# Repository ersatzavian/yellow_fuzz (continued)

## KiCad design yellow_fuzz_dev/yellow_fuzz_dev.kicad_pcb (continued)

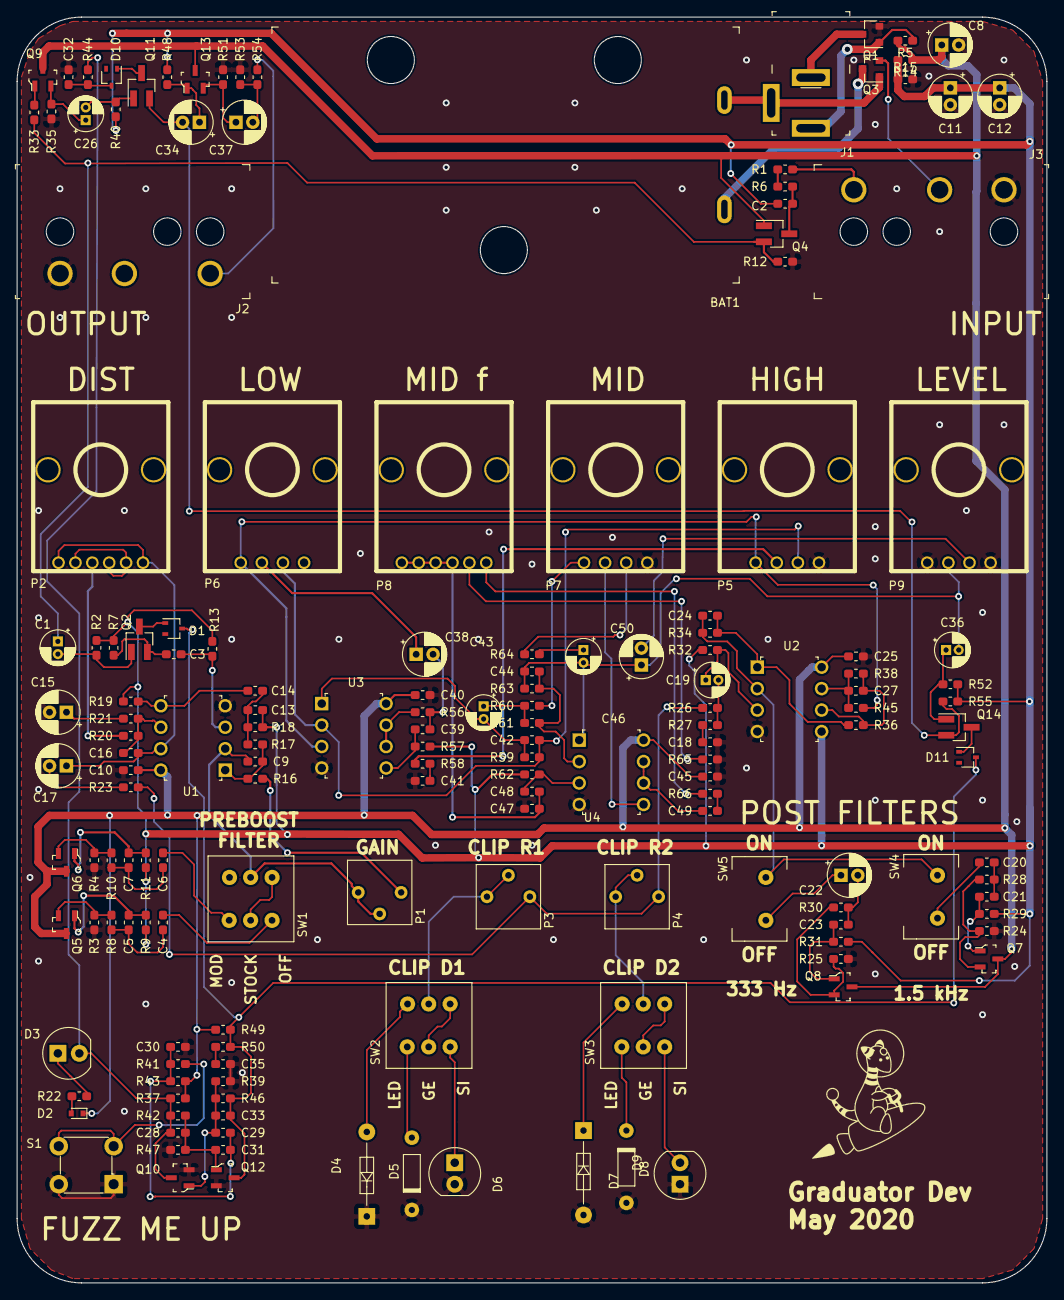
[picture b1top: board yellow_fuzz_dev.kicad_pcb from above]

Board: 2 copper layers, 121.9 x 149.9 mm, 164 parts (0 on the bottom side), 106 nets.

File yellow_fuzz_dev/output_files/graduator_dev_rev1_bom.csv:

"Id";"Designator";"Package";"Quantity";"Designation";"Supplier and ref";
1;"P4,P3";"3362PT";2;"3362P-1-102TLF";;;
2;"C40,C48,C45,C25,C10,C4";"C_0603_1608Metric_Pad1.05x0.95mm_HandSolder";6;"0.1u";;;
3;"G***";"amph_1_5x1_5";1;"LOGO";;;
4;"P9";"Potentiometer_Bourns_PTV111_4420A_Single_Vertical";1;"PTV111-4420A-A503";;;
5;"P8";"Potentiometer_Bourns_PTV112_3417A_Dual_Vertical";1;"PTV112-4420A-A503";;;
6;"P7,P6,P5";"Potentiometer_Bourns_PTV111_4420A_Single_Vertical";3;"PTV111-4420A-A104";;;
7;"P2";"Potentiometer_Bourns_PTV112_3417A_Dual_Vertical";1;"PTV112-4420A-A104";;;
8;"BAT1";"Battery_Holder_9V_BC9VPC-ND";1;"BC9VPC";;;
9;"J2";"Headphone_Jack_6.35mm_SN49B12B";1;"RA49B11";;;
10;"J3";"Headphone_Jack_6.35mm_SN49B12B";1;"SN49B12B";;;
11;"J1";"Barrel_Jack_5.5mmODx2.1mmID_PJ-202A";1;"PJ-202A";;;
12;"U4,U3,U2,U1";"DIP-8_W7.62mm";4;"TL072CP";;;
13;"S1";"Switch_Tactile_THT_6x6mm";1;"1825910-6";;;
14;"C50,C37,C34,C17,C15";"CP_Radial_D5.0mm_P2.00mm";5;"10u";;;
15;"C46,C43,C36,C26,C19,C1";"CP_Radial_D4.0mm_P1.50mm";6;"1u";;;
16;"C38,C22";"CP_Radial_D5.0mm_P2.00mm";2;"220n";;;
17;"C12,C11,C8";"CP_Radial_D5.0mm_P2.00mm";3;"100u";;;
18;"Q6,Q12,Q10,Q9,Q8,Q7,Q5,Q13";"SOT-23-3";8;"BC817-25-TP";;;
19;"D8,D5";"DO-35";2;"1N34A";;;
20;"D7,D4";"Diode_DO-35_P10mm";2;"1N4148";;;
21;"D9,D6,D3";"LED_5mm_Radial";3;"WP7113QBC_D";;;
22;"R66,R65,R58,R56,R23,R10,R8";"R_0603_1608Metric_Pad1.05x0.95mm_HandSolder";7;"2.2k";;;
23;"R64,R60";"R_0603_1608Metric_Pad1.05x0.95mm_HandSolder";2;"330";;;
24;"R63,R61,R29,R11,R9";"R_0603_1608Metric_Pad1.05x0.95mm_HandSolder";5;"47k";;;
25;"R62,R55,R52,R50,R44,R43,R40,R7,R6";"R_0603_1608Metric_Pad1.05x0.95mm_HandSolder";9;"1M";;;
26;"R59,R45,R38,R36";"R_0603_1608Metric_Pad1.05x0.95mm_HandSolder";4;"22k";;;
27;"R57,R53,R48,R46,R42,R32,R19,R13,R2";"R_0603_1608Metric_Pad1.05x0.95mm_HandSolder";9;"100k";;;
28;"R54,R28,R21,R20,R16";"R_0603_1608Metric_Pad1.05x0.95mm_HandSolder";5;"1k";;;
29;"R51,R35,R33,R26,R25,R24,R18,R17,R15,R14,R12,R4,R3,R1";"R_0603_1608Metric_Pad1.05x0.95mm_HandSolder";14;"10k";;;
30;"R49,R47,R39,R37";"R_0603_1608Metric_Pad1.05x0.95mm_HandSolder";4;"56k";;;
31;"R41";"R_0603_1608Metric_Pad1.05x0.95mm_HandSolder";1;"100";;;
32;"R34";"R_0603_1608Metric_Pad1.05x0.95mm_HandSolder";1;"3.3k";;;
33;"R31";"R_0603_1608Metric_Pad1.05x0.95mm_HandSolder";1;"470k";;;
34;"R30";"R_0603_1608Metric_Pad1.05x0.95mm_HandSolder";1;"470";;;
35;"R27";"R_0603_1608Metric_Pad1.05x0.95mm_HandSolder";1;"4.7k";;;
36;"R22";"R_0603_1608Metric_Pad1.05x0.95mm_HandSolder";1;"1.2k";;;
37;"R5";"R_0603_1608Metric_Pad1.05x0.95mm_HandSolder";1;"22";;;
38;"Q14,Q11,Q4,Q2";"SOT-23_Handsoldering";4;"NSVJ3910SB3T1GOSCT-ND";;;
39;"Q3,Q1";"SOT-23";2;"DMN2041L";;;
40;"D11,D10,D1";"SOT-323_SC-70";3;"BAS16W";;;
41;"D2";"D_SOD-523";1;"DZ2S056X0L";;;
42;"C49";"C_0603_1608Metric_Pad1.05x0.95mm_HandSolder";1;"22n";;;
43;"C47";"C_0603_1608Metric_Pad1.05x0.95mm_HandSolder";1;"8.2n";;;
44;"C44,C9";"C_0603_1608Metric_Pad1.05x0.95mm_HandSolder";2;"100p";;;
45;"C42,C27";"C_0603_1608Metric_Pad1.05x0.95mm_HandSolder";2;"10p";;;
46;"C41,C30,C7";"C_0603_1608Metric_Pad1.05x0.95mm_HandSolder";3;"10n";;;
47;"C39,C35,C32,C23,C13,C5,C2";"C_0603_1608Metric_Pad1.05x0.95mm_HandSolder";7;"47n";;;
48;"C33,C28";"C_0603_1608Metric_Pad1.05x0.95mm_HandSolder";2;"470p";;;
49;"C31,C29";"C_0603_1608Metric_Pad1.05x0.95mm_HandSolder";2;"220p";;;
50;"C24,C16";"C_0603_1608Metric_Pad1.05x0.95mm_HandSolder";2;"47p";;;
51;"C21";"C_0603_1608Metric_Pad1.05x0.95mm_HandSolder";1;"1.5n";;;
52;"C20,C18";"C_0603_1608Metric_Pad1.05x0.95mm_HandSolder";2;"15n";;;
53;"C14";"C_0603_1608Metric_Pad1.05x0.95mm_HandSolder";1;"33n";;;
54;"C6";"C_0603_1608Metric_Pad1.05x0.95mm_HandSolder";1;"27n";;;
55;"C3";"C_0603_1608Metric_Pad1.05x0.95mm_HandSolder";1;"1.0u";;;
56;"SW5,SW4";"A11JP";2;"SW_SPST_A11JP";;;
57;"SW3,SW2,SW1";"A24JP";3;"SW_SP3T_A24JP";;;
58;"P1";"3386P";1;"3386P-1-204TLF";;;

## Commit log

2019-12-01 created sim of fairfield barbershop overdrive
2020-01-24 did a bunch of sims and made a readme, schematic capture time
2020-01-31 sourced all resistors and caps, need to create new footprints for potentiometers.
2020-01-31 readme update
2020-02-02 adding footprints for new pots
2020-02-04 added some new candidate parts
2020-02-04 pulling parts in for schematic capture
2020-02-04 removed solved parts from readme list
2020-02-04 noted footswitch part number
2020-02-06 schematic capture in progress
2020-02-13 placing symbols for EQ section
2020-03-29 captured tone, power, and switching sections.
2020-03-29 added power jack
2020-04-03 power section and interconnect done
2020-04-03 Changed qual op amps to duals for easy swapping
2020-04-03 reviewing all filter setpoints, just made it to distortion section
2020-04-21 woo boy I dunno buncha progress probably
2020-04-22 moved footprints into PCB
2020-04-22 added 3d to connector and DIP footprints, moved to project lib, updated PCB
2020-04-27 updated potentiometers to use the same mechanical family throughout
2020-04-28 placement partially done
2020-04-28 first draft placement done. Added ampharos logo.
2020-04-30 did a bunch of routing and rounded the corners
2020-05-01 routing complete and DRC clear
2020-05-02 BOM messings-about. Kicad is terrible at this
2020-05-02 corrected BOM fields and generated BOM
2020-05-02 generated gerbers, BOM, and sch - releasing dev to fab
2020-05-02 regenerated gerbers and drill files
2020-05-02 saving changes?
2020-09-07 rev1 build in progress, updated issue notes in readme.
2020-09-29 bringup updates.
2020-09-29 fixed markdown for images again
2020-09-29 I should really be using markdown preview
2020-09-30 updated bringup notes for Rev01
2020-10-11 Finished Rev01 build and bringup, on to building SN02 and SN03, and play testing
2020-11-11 updated user guide
2020-11-11 added labeled controls picture
2020-11-11 fixed user guide image link
2021-09-15 created form-factor project directory, copied project over and resolved library bcrap, added board outline sketch, added symbols for new threaded pots to library, still need footprints.
2021-09-20 added new potentiometer footprint to lib but it isn't linked right yet
